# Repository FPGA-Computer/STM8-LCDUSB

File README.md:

# STM8-LCDUSB

The firmware only USB stack is an unofficial fork from STM8S-VUSB-KEYBOARD at https://github.com/BBS215/STM8S-VUSB-KEYBOARD

- Russian comments "google translated" to English.  Minimal changes to the original are in .zip file.

- Works with current special edition of Cosmic C (4.4.10) and current version of STVD (4.3.12)

STM8 LCD2USB

- LCD2USB port from ATMega8 to STM8S003. It is working with LCD Smarties.  Only 1 LCD controller supported i.e. no support for larger display. If the LCD is accessed with delays (Not implemented) instead of polling, the GPIO for R/W can be repurposed as Enable pin (E).

LCD2USB at https://github.com/harbaum/LCD2USB  (LCD2USB.dll)

LCD Smarties at http://lcdsmartie.sourceforge.net/

- USB stack logic is modified for this tech demo. Vendor Request packets (needed by LCD2USB) is working.  HID not tested yet.

- Code reformatted/refractored.  Using my own IRQ files for STM8S003 for a much cleaner organization.  

- No longer need a separate GPIO for the 1.5K pull up to connect/disconnect USB.  See schematic.

- Device library calls have been changed to bare metal to minimized dependancy and reduce code size.  stm8s_flash.c is the only library needed.

- "Port C pins can only be used as GPIO inputs" is no longer the case. They can be configured as PWM and force them Low/High via CCMRx registers.  See hardware.h

- The PCB is a general purpose single sided PCB. Serial port, I2C are broken out to headers, pads for tiny crystal and load capacitors available for oscillator. 
The buttons are also used as jumpers for Gnd.  Install 2 jumpers under buttons S1 and S2 if they are not used.  LCD mounting holes and pinouts are for common 1602A from China.

- Not sure if the buttons (S1 & S3) are working correctly. LCD2USB.dll for LCD Smarties does not seem to access them directly. I don't know LCD Smarties enough.  The AVR firmware doesn't debunce them.

Note: 

The USB stack calibrates the HSI clock while connected to the PC. The calibration is store in EEPROM. It can take a couple of minutes the first time before it functions correctly.

Timer 1 is used by the USB stack for filtering and interrupt. It is not actually used for counting.

R7 value control brightness.  I use R7 = 330R for my green display and 2.7K for my white ones.

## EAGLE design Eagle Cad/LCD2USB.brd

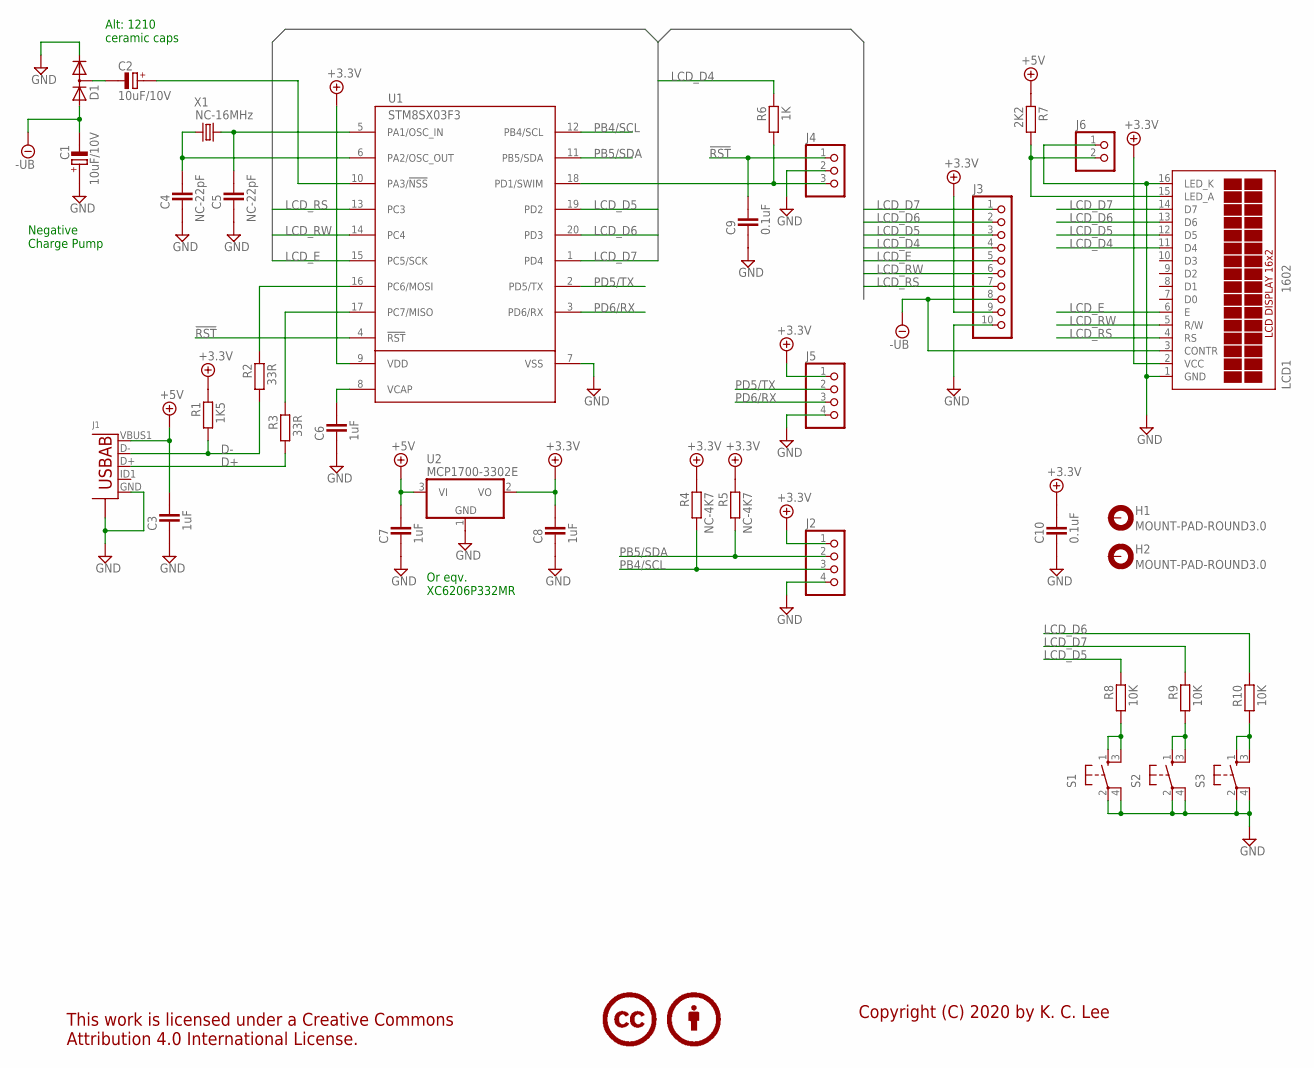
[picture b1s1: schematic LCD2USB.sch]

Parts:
C1, C2: 10uF/10V; CAPMP3528X210N
C3, C6, C7, C8: 1uF; CAPC1608X92N
C4, C5: NC-22pF; CAPC1608X92N
C9, C10: 0.1uF; CAPC1608X92N
D1: KA2KA_SOT-23; SOT95P280X135-3N
H1, H2: MOUNT-PAD-ROUND3.0; 3,0-PAD
J1: USB-ABBG-ORG; USB-AB-MICRO-SMD_V03_SMT
J2, J5: PINHD-1X4_2.54-90°; 1X04/90
J3: PINHD-1X10_2.54; 1X10
J4: PINHD-1X3_2.54-90°; 1X03/90
J6: PINHD-1X2_2.54; 1X02
LCD1: 1602; TUXGR_16X2_R2_NM
LICENSE1: CC-BY100%; CC-BY-100
R1: 1K5; RESC1608X55N
R2, R3: 33R; RESC2012X70N
R4, R5: NC-4K7; RESC1608X55N
R6: 1K; RESC1608X55N
R7: 2K2; RESC1608X55N
R8, R9, R10: 10K; RESC2012X70N
S1, S2, S3: MOM_SWTH; MOM_SW
U1: STM8SX03F3; TSSOP20
U2: MCP1700-3302E; SOT95P280X135-3N
X1: NC-16MHz; TC26H

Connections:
!RST: C9.2, J4.1, U1.4 (!RST)
+3.3V: C8.2, C10.2, J2.1, J3.9, J5.1, LCD1.2 (VCC), R1.1, R4.1, R5.1, U1.9 (VDD), U2.2 (VO)
+5V: C3.2, C7.2, J1.VBUS1 (VBUS), R7.1, U2.3 (VI)
-UB: C1.-, D1.1 (A), J3.8, LCD1.3 (CONTR)
D+: J1.D+, R3.2
D-: J1.D-, R1.2, R2.2
GND: C1.+, C3.1, C4.1, C5.1, C6.1, C7.1, C8.1, C9.1, C10.1, D1.2 (K), J1.GND, J1.S1 (S), J1.S2 (S), J1.S3 (S), J1.S4 (S), J2.4, J3.10, J4.2, J5.4, J6.1, LCD1.1 (GND), LCD1.16 (LED_K), S1.2 (3), S1.4, S2.2 (3), S2.4, S3.2 (3), S3.4, U1.7 (VSS), U2.1 (GND)
LCD_A: J6.2, LCD1.15 (LED_A), R7.2
LCD_D4: J3.4, LCD1.11 (D4), R6.1
LCD_D5: J3.3, LCD1.12 (D5), R8.1, U1.19 (PD2)
LCD_D6: J3.2, LCD1.13 (D6), R10.1, U1.20 (PD3)
LCD_D7: J3.1, LCD1.14 (D7), R9.1, U1.1 (PD4)
LCD_E: J3.5, LCD1.6 (E), U1.15 (PC5/SCK)
LCD_RS: J3.7, LCD1.4 (RS), U1.13 (PC3)
LCD_RW: J3.6, LCD1.5 (R/W), U1.14 (PC4)
unnamed: C6.2, U1.8 (VCAP)
unnamed: R3.1, U1.17 (PC7/MISO)
unnamed: C5.2, U1.5 (PA1/OSC_IN), X1.1
unnamed: C4.2, U1.6 (PA2/OSC_OUT), X1.2
unnamed: R2.1, U1.16 (PC6/MOSI)
unnamed: R8.2, S1.1, S1.3 (2)
unnamed: C2.+, U1.10 (PA3/!NSS)
unnamed: C2.-, D1.3 (KA)
unnamed: J4.3, R6.2, U1.18 (PD1/SWIM)
unnamed: R9.2, S2.1, S2.3 (2)
unnamed: R10.2, S3.1, S3.3 (2)
PB4/SCL: J2.3, R4.2, U1.12 (PB4/SCL)
PB5/SDA: J2.2, R5.2, U1.11 (PB5/SDA)
PD5/TX: J5.2, U1.2 (PD5/TX)
PD6/RX: J5.3, U1.3 (PD6/RX)

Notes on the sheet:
Copyright (C) 2020 by K. C. Lee
Negative Charge Pump
Alt: 1210 ceramic caps
Or eqv. XC6206P332MR

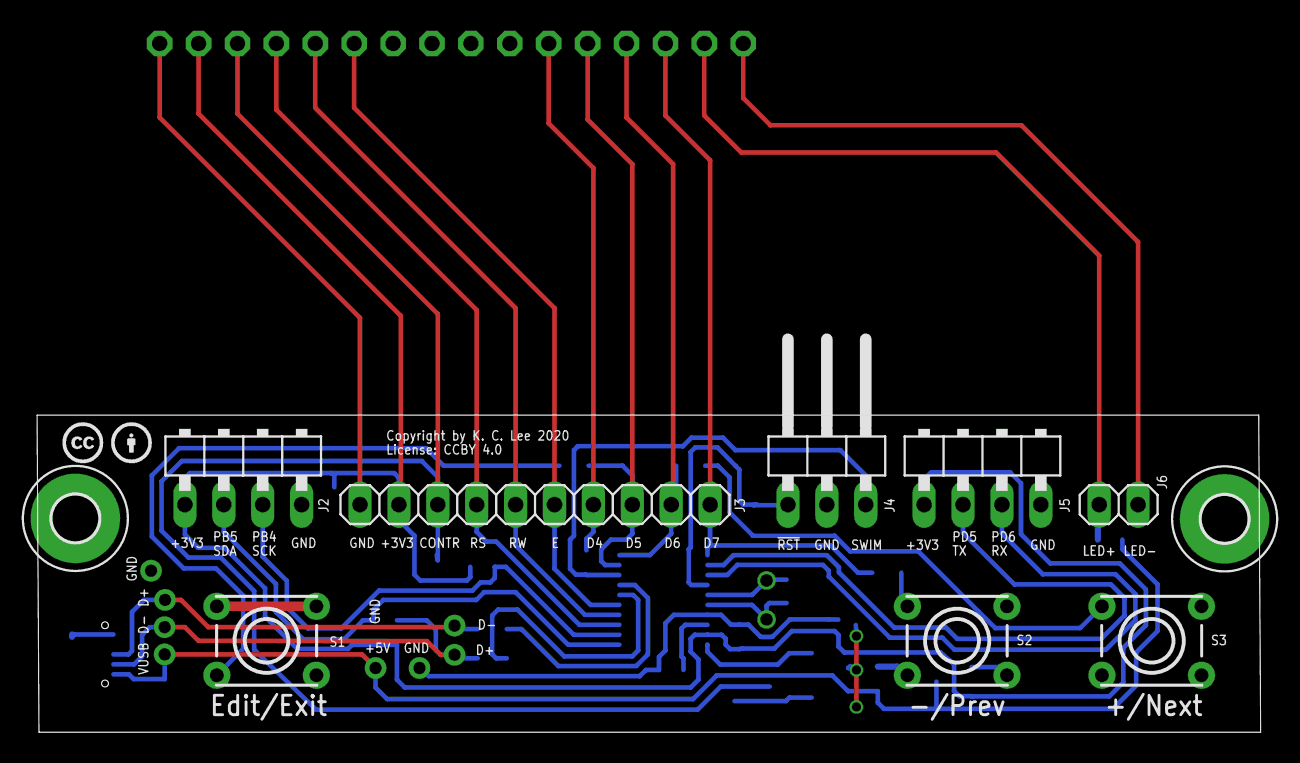
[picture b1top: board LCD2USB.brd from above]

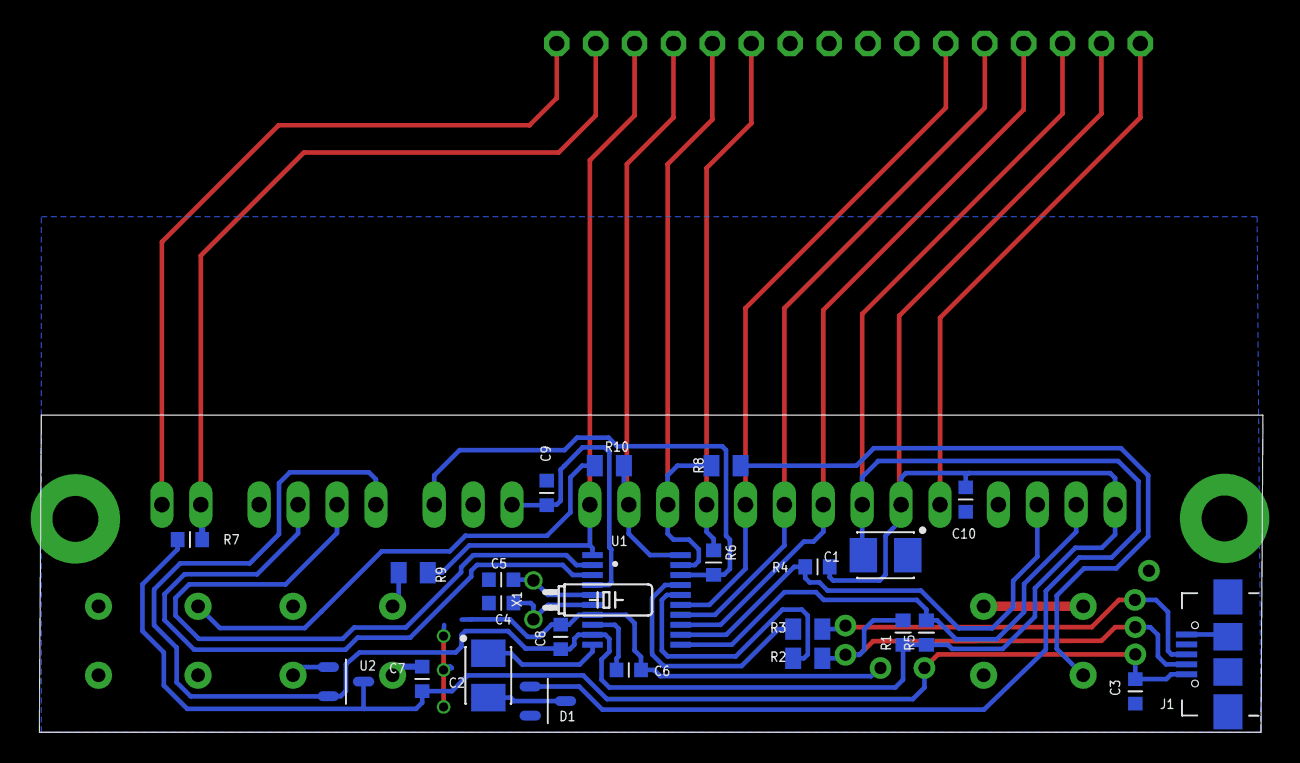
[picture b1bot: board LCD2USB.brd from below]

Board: 2 copper layers, 79.9 x 20.7 mm, 37 parts (25 on the bottom side), 30 nets.

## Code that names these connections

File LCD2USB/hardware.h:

/*
 * hardware.h
 *
 * Created: October 31, 2019, 12:33:01 PM
 *  Author: K. C. Lee
 * Copyright (c) 2019 by K. C. Lee
 
 This program is free software: you can redistribute it and/or modify
 it under the terms of the GNU General Public License as published by
 the Free Software Foundation, either version 3 of the License, or
 (at your option) any later version.

 This program is distributed in the hope that it will be useful,
 but WITHOUT ANY WARRANTY; without even the implied warranty of
 MERCHANTABILITY or FITNESS FOR A PARTICULAR PURPOSE.  See the
 GNU General Public License for more details.

 You should have received a copy of the GNU General Public License
 along with this program.

 If not, see http://www.gnu.org/licenses/gpl-3.0.en.html 
 */ 

#ifndef HARDWARE_H_
#define HARDWARE_H_

#ifndef __CSMC__
#define __CSMC__
#endif
#ifndef STM8S003
#define STM8S003
#endif

#include "stm8s.h"
#include <stdio.h>

// STM8S003F3P6
enum _PA { PA1=0x02, PA2=0x04, PA3=0x08 };
enum _PB { PB4=0x10, PB5=0x20 };
enum _PC { PC3=0x08, PC4=0x10, PC5=0x20, PC6=0x40, PC7=0x80 };
enum _PD { PD1=0x02, PD2=0x04, PD3=0x08, PD4=0x10, PD5=0x20, PD6=0x40 };

#define GPIO(X)					((GPIO_TypeDef *)(X))

#define CPU_CLOCK				16000000UL
#define EE_Addr					0x4000

#define LCD_BIAS_PORT		GPIOA
#define LCD_BIAS_PIN		PA3

enum _OPT2 { AFR0 = 0x01, AFR1=0x02, AFR2=0x04, AFR3=0x08, AFR4=0x10, AFR5=0x20, AFR6=0x40, AFR7 = 0x80 };
enum _OPT3 { HSITRIM = 0x10, LSI_EN = 0x08, IWDG_HW = 0x04, WWDG_HW = 0x02, WWDG_HALT = 0x01 };

#define TIM2_PRSC				4
#define TIM2_FREQ				400
#define TIM2_Slow				100
#define TIM2_CNTMAX			(TIM2_FREQ/TIM2_Slow)
#define TIM2_RELOAD			(CPU_CLOCK/(1<<TIM2_PRSC)/TIM2_FREQ)

// fake output for PC[5..3]

// Control PC5
#define Clr_PC5()				TIM2->CCMR1 = (0x4<<4)
#define Set_PC5()				TIM2->CCMR1 = (0x5<<4)
#define Clr_PC4()				TIM1->CCMR4 = (0x4<<4)
#define Set_PC4()				TIM1->CCMR4 = (0x5<<4)
#define Clr_PC3()				TIM1->CCMR3 = (0x4<<4)
#define Set_PC3()				TIM1->CCMR3 = (0x5<<4)

// LCD GPIO mapping
#define Clr_LCD_E()			Clr_PC5()
#define Set_LCD_E()			Set_PC5()
#define Clr_LCD_RW()		Clr_PC4()
#define Set_LCD_RW()		Set_PC4()
#define Clr_LCD_RS()		Clr_PC3()
#define Set_LCD_RS()		Set_PC3()

#define LCD_DATA_PORT		GPIOD
#define LCD_DATA				(PD4|PD3|PD2|PD1)
#define LCD_DOFFSET			1
#define KEY_DOFFSET			(LCD_DOFFSET+1)

extern volatile uint8_t TIM2_Update_Flag;

void Init_Hardware(void);
void RESET_CHIP(void);
void Check_OPTION_BYTE(void);
void FLASH_Data_lock(uint8_t lock);
void FLASH_Wait(void);
void TIM2_Init(void);

void LCD_Init(void);
void Delay(uint16_t t);
uint8_t Key_Get(void);

// Delays in us.  The delay has been calibrated for 16MHz
// Maximum delay is about 100ms (16-bit)

#define DELAY_TWEAK			0.63
#define US_DELAY(X)			((uint16_t)(X*DELAY_TWEAK))

typedef struct
{
	uint8_t code;
	uint8_t count;
} key_t;

extern key_t key;

void KeyScan(void);

#define KEY_REPEAT_RATE		4
#define KEY_THRESHOLD			3
#define KEY_REPEAT_WAIT		0.75

#define KEY_CNT_MAX				(KEY_REPEAT_WAIT*TIM2_Slow+KEY_THRESHOLD)
#define KEY_RELOAD				(KEY_CNT_MAX-TIM2_Slow/KEY_REPEAT_RATE)

enum keys { KEY_MENU=0x01, KEY_DEC=0x02, KEY_INC=0x04, KEY_MASK= KEY_MENU|KEY_DEC|KEY_INC, 
						KEY_LONG=0x10, KEY_REPORTED=0x40, KEY_FLAG=0x80 };
						
#endif

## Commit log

2020-08-18 Initial release
2020-08-20 Add LCD GPIO init
2020-08-20 add LCD stand
2020-08-20 Add button support - STM8_LCD2USB.dll
2020-08-20 tweak buttons parms
2020-08-20 fixing readme.md vs README.md - finger crossed
2020-09-17 VUSB library update - added HID support
2021-03-04 keep usb lib up to date
2021-03-08 Removed library - smaller code

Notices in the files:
Eagle Cad/LCD2USB.brd:
Copyright by K. C. Lee 2020
License: CCBY 4.0
parts and their libraries:
Misc logo: This work is licensed under a Creative Commons
Attribution 4.0 International License.
